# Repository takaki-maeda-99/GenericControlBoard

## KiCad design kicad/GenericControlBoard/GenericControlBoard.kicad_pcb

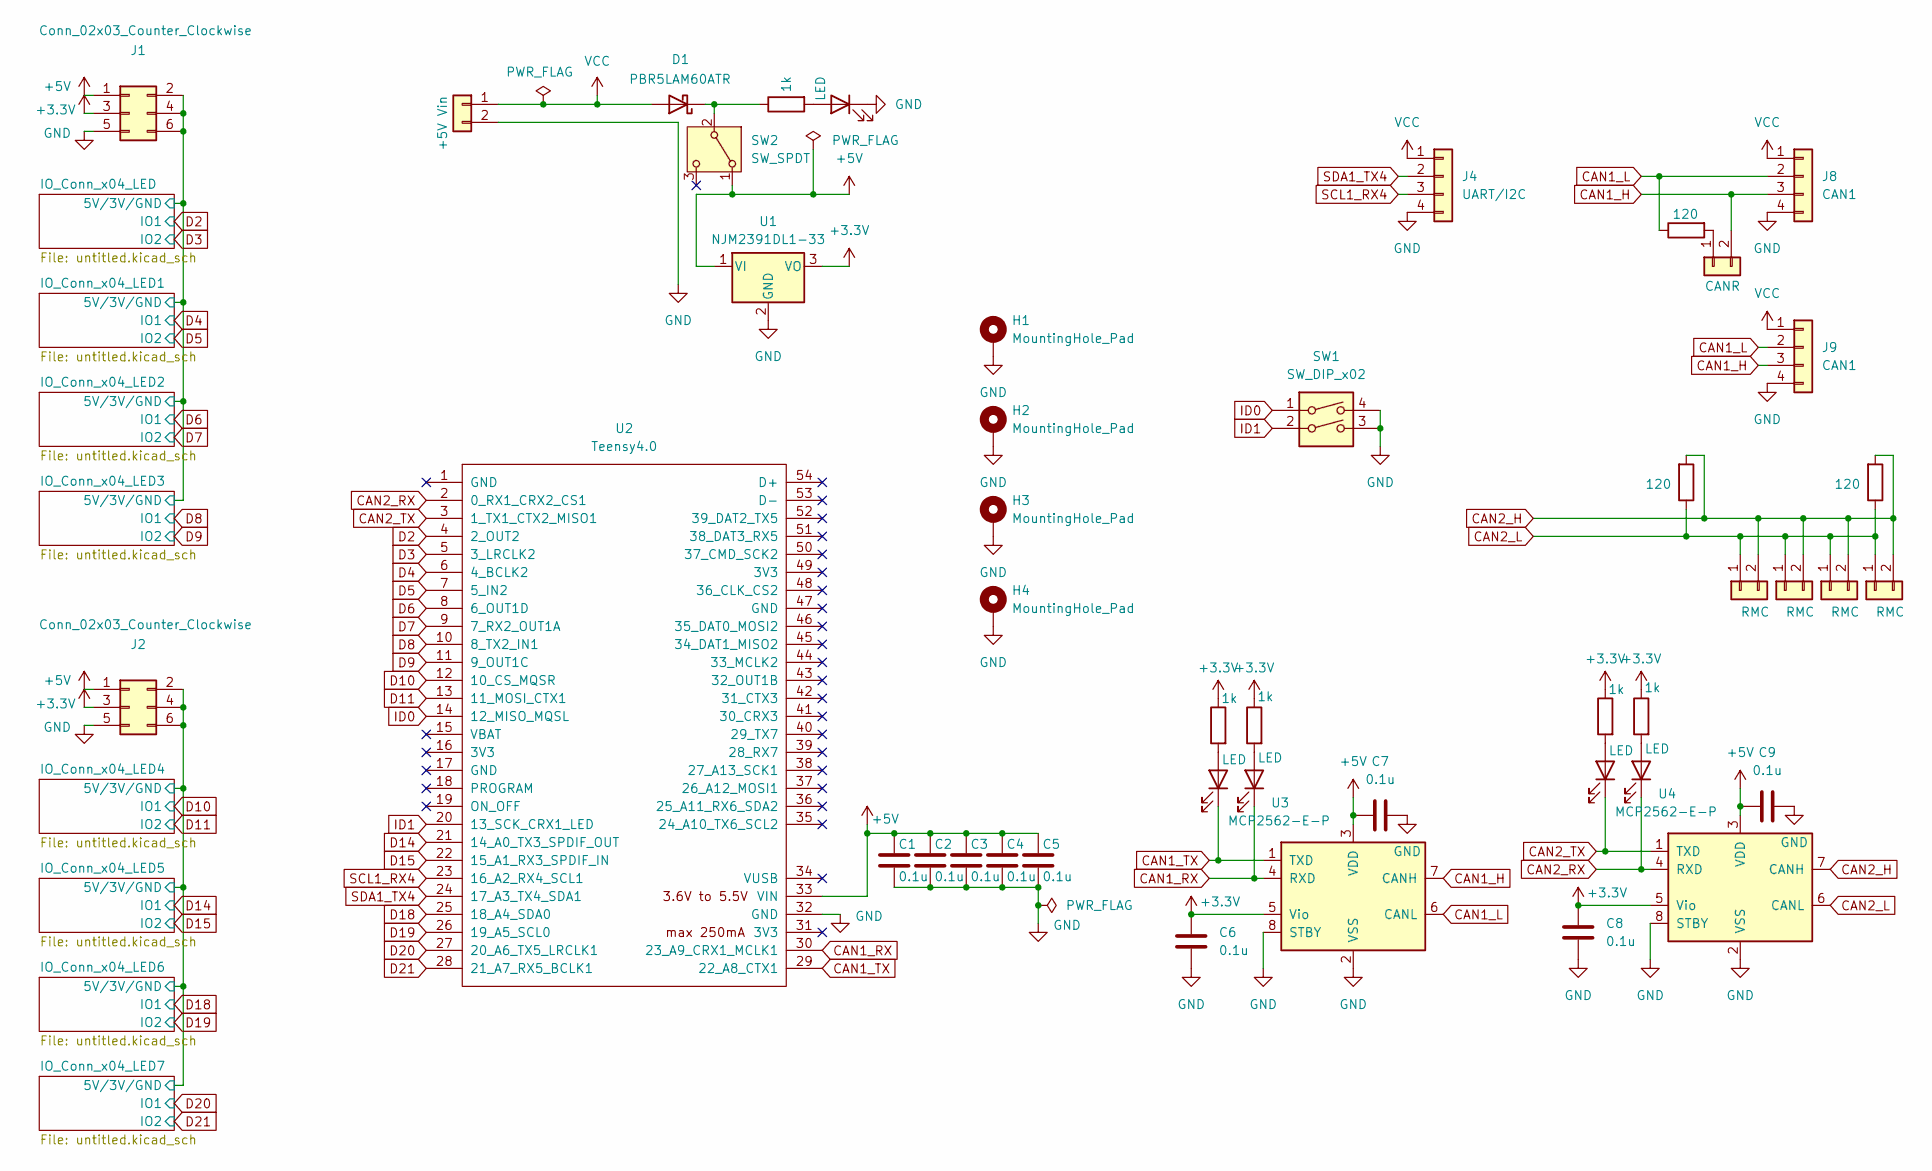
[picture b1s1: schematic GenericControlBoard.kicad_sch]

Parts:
C1, C2, C3, C4, C5, C6, C7, C8, C9: 0.1u; C_0603_1608Metric
D1: PBR5LAM60ATR; D_SOD-128
D2, D3, D22, D23, D24: LED; LED_0603_1608Metric
H1, H2, H3, H4: MountingHole_Pad; MountingHole_3.2mm_M3_DIN965_Pad
J1, J2: Conn_02x03_Counter_Clockwise; PinHeader_2x03_P2.54mm_Vertical
J3: +5V Vin; JST_XH_S2B-XH-A_1x02_P2.50mm_Horizontal
J4: UART/I2C; JST_XH_S4B-XH-A_1x04_P2.50mm_Horizontal
J5: CANR; PinSocket_1x02_P2.54mm_Vertical
J6, J7, J10, J11: RMC; JST_XH_S2B-XH-A_1x02_P2.50mm_Horizontal
J8, J9: CAN1; JST_XH_S4B-XH-A_1x04_P2.50mm_Horizontal
R1, R2, R24, R25, R26: 1k; R_0603_1608Metric
R4, R5, R7: 120; R_0603_1608Metric
SW1: SW_DIP_x02; SW_DIP_SPSTx02_Slide_9.78x7.26mm_W7.62mm_P2.54mm
SW2: SW_SPDT; FanPinHeader_1x03_P2.54mm_Vertical
U1: NJM2391DL1-33; TO-252-2
U2: Teensy4.0; Teensy40
U3, U4: MCP2562-E-P; DIP-8_W7.62mm

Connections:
+3.3V: C6.2, C8.2, J1.3, J2.3, R1.1, R2.1, R25.1, R26.1, U1.3 (VO), U3.5 (Vio), U4.5 (Vio); also elsewhere on the board
+5V: C1.1, C2.1, C3.1, C4.1, C5.1, C7.2, C9.2, J1.1, J2.1, SW2.1 (A), U1.1 (VI), U2.33 (VIN), U3.3 (VDD), U4.3 (VDD)
/IO_Conn_x04_LED4/5V/3V/GND: J2.2, J2.4, J2.6; also elsewhere on the board
/IO_Conn_x04_LED/5V/3V/GND: J1.2, J1.4, J1.6; also elsewhere on the board
CAN1_H: J5.2, J8.3, J9.3, U3.7 (CANH)
CAN1_L: J8.2, J9.2, R4.1, U3.6 (CANL)
CAN1_RX: D24.1 (K), U2.30 (23_A9_CRX1_MCLK1), U3.4 (RXD)
CAN1_TX: D23.1 (K), U2.29 (22_A8_CTX1), U3.1 (TXD)
CAN2_H: J6.2, J7.2, J10.2, J11.2, R5.2, R7.2, U4.7 (CANH)
CAN2_L: J6.1, J7.1, J10.1, J11.1, R5.1, R7.1, U4.6 (CANL)
CAN2_RX: D3.1 (K), U2.2 (0_RX1_CRX2_CS1), U4.4 (RXD)
CAN2_TX: D2.1 (K), U2.3 (1_TX1_CTX2_MISO1), U4.1 (TXD)
D2: U2.4 (2_OUT2); also elsewhere on the board
D3: U2.5 (3_LRCLK2); also elsewhere on the board
D4: U2.6 (4_BCLK2); also elsewhere on the board
D5: U2.7 (5_IN2); also elsewhere on the board
D6: U2.8 (6_OUT1D); also elsewhere on the board
D7: U2.9 (7_RX2_OUT1A); also elsewhere on the board
D8: U2.10 (8_TX2_IN1); also elsewhere on the board
D9: U2.11 (9_OUT1C); also elsewhere on the board
D10: U2.12 (10_CS_MQSR); also elsewhere on the board
D11: U2.13 (11_MOSI_CTX1); also elsewhere on the board
D14: U2.21 (14_A0_TX3_SPDIF_OUT); also elsewhere on the board
D15: U2.22 (15_A1_RX3_SPDIF_IN); also elsewhere on the board
D18: U2.25 (18_A4_SDA0); also elsewhere on the board
D19: U2.26 (19_A5_SCL0); also elsewhere on the board
D20: U2.27 (20_A6_TX5_LRCLK1); also elsewhere on the board
D21: U2.28 (21_A7_RX5_BCLK1); also elsewhere on the board
GND: C1.2, C2.2, C3.2, C4.2, C5.2, C6.1, C7.1, C8.1, C9.1, D22.1 (K), H1.1, H2.1, H3.1, H4.1, J1.5, J2.5, J3.2, J4.4, J8.4, J9.4, SW1.3, SW1.4, U1.2 (GND), U2.32 (GND), U3.2 (VSS), U3.8 (STBY), U4.2 (VSS), U4.8 (STBY); also elsewhere on the board
ID0: SW1.1, U2.14 (12_MISO_MQSL)
ID1: SW1.2, U2.20 (13_SCK_CRX1_LED)
unnamed: D1.1 (K), R24.1, SW2.2 (B)
unnamed: D2.2 (A), R1.2
unnamed: D3.2 (A), R2.2
unnamed: D22.2 (A), R24.2
unnamed: D23.2 (A), R25.2
unnamed: D24.2 (A), R26.2
unnamed: J5.1, R4.2
SCL1_RX4: J4.3, U2.23 (16_A2_RX4_SCL1)
SDA1_TX4: J4.2, U2.24 (17_A3_TX4_SDA1)
VCC: D1.2 (A), J3.1, J4.1, J8.1, J9.1

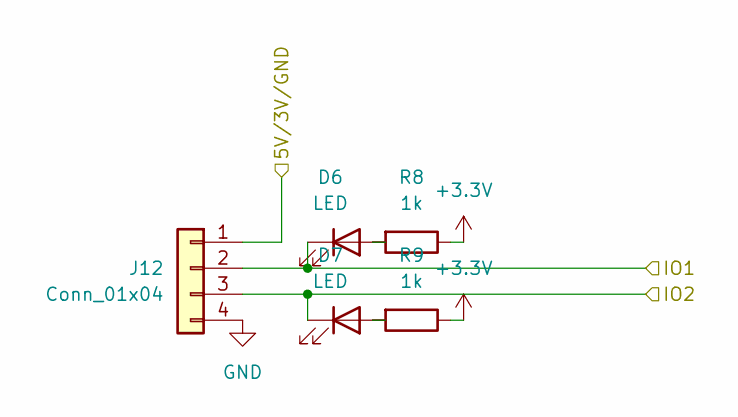
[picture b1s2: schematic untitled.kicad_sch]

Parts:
D6, D7: LED; LED_0603_1608Metric
J12: Conn_01x04; JST_XH_S4B-XH-A_1x04_P2.50mm_Horizontal
R8, R9: 1k; R_0603_1608Metric

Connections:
+3.3V: R8.1, R9.1; also elsewhere on the board
/IO_Conn_x04_LED/5V/3V/GND: J12.1; also elsewhere on the board
D2: D6.1 (K), J12.2; also elsewhere on the board
D3: D7.1 (K), J12.3; also elsewhere on the board
GND: J12.4; also elsewhere on the board
unnamed: D6.2 (A), R8.2
unnamed: D7.2 (A), R9.2

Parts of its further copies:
D8, D9, D10, D11, D12, D13, D14, D15, D16, D17, D18, D19, D20, D21: LED; LED_0603_1608Metric
J13, J14, J15, J16, J17, J18, J19: Conn_01x04; JST_XH_S4B-XH-A_1x04_P2.50mm_Horizontal
R10, R11, R12, R13, R14, R15, R16, R17, R18, R19, R20, R21, R22, R23: 1k; R_0603_1608Metric

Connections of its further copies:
+3.3V: R10.1, R11.1, R12.1, R13.1, R14.1, R15.1, R16.1, R17.1, R18.1, R19.1, R20.1, R21.1, R22.1, R23.1; also elsewhere on the board
/IO_Conn_x04_LED4/5V/3V/GND: J16.1, J17.1, J18.1, J19.1; also elsewhere on the board
/IO_Conn_x04_LED/5V/3V/GND: J13.1, J14.1, J15.1; also elsewhere on the board
D4: D8.1 (K), J13.2; also elsewhere on the board
D5: D9.1 (K), J13.3; also elsewhere on the board
D6: D10.1 (K), J14.2; also elsewhere on the board
D7: D11.1 (K), J14.3; also elsewhere on the board
D8: D12.1 (K), J15.2; also elsewhere on the board
D9: D13.1 (K), J15.3; also elsewhere on the board
D10: D14.1 (K), J16.2; also elsewhere on the board
D11: D15.1 (K), J16.3; also elsewhere on the board
D14: D16.1 (K), J17.2; also elsewhere on the board
D15: D17.1 (K), J17.3; also elsewhere on the board
D18: D18.1 (K), J18.2; also elsewhere on the board
D19: D19.1 (K), J18.3; also elsewhere on the board
D20: D20.1 (K), J19.2; also elsewhere on the board
D21: D21.1 (K), J19.3; also elsewhere on the board
GND: J13.4, J14.4, J15.4, J16.4, J17.4, J18.4, J19.4; also elsewhere on the board
unnamed: D8.2 (A), R10.2
unnamed: D9.2 (A), R11.2
unnamed: D10.2 (A), R12.2
unnamed: D11.2 (A), R13.2
unnamed: D12.2 (A), R14.2
unnamed: D13.2 (A), R15.2
unnamed: D14.2 (A), R16.2
unnamed: D15.2 (A), R17.2
unnamed: D16.2 (A), R18.2
unnamed: D17.2 (A), R19.2
unnamed: D18.2 (A), R20.2
unnamed: D19.2 (A), R21.2
unnamed: D20.2 (A), R22.2
unnamed: D21.2 (A), R23.2

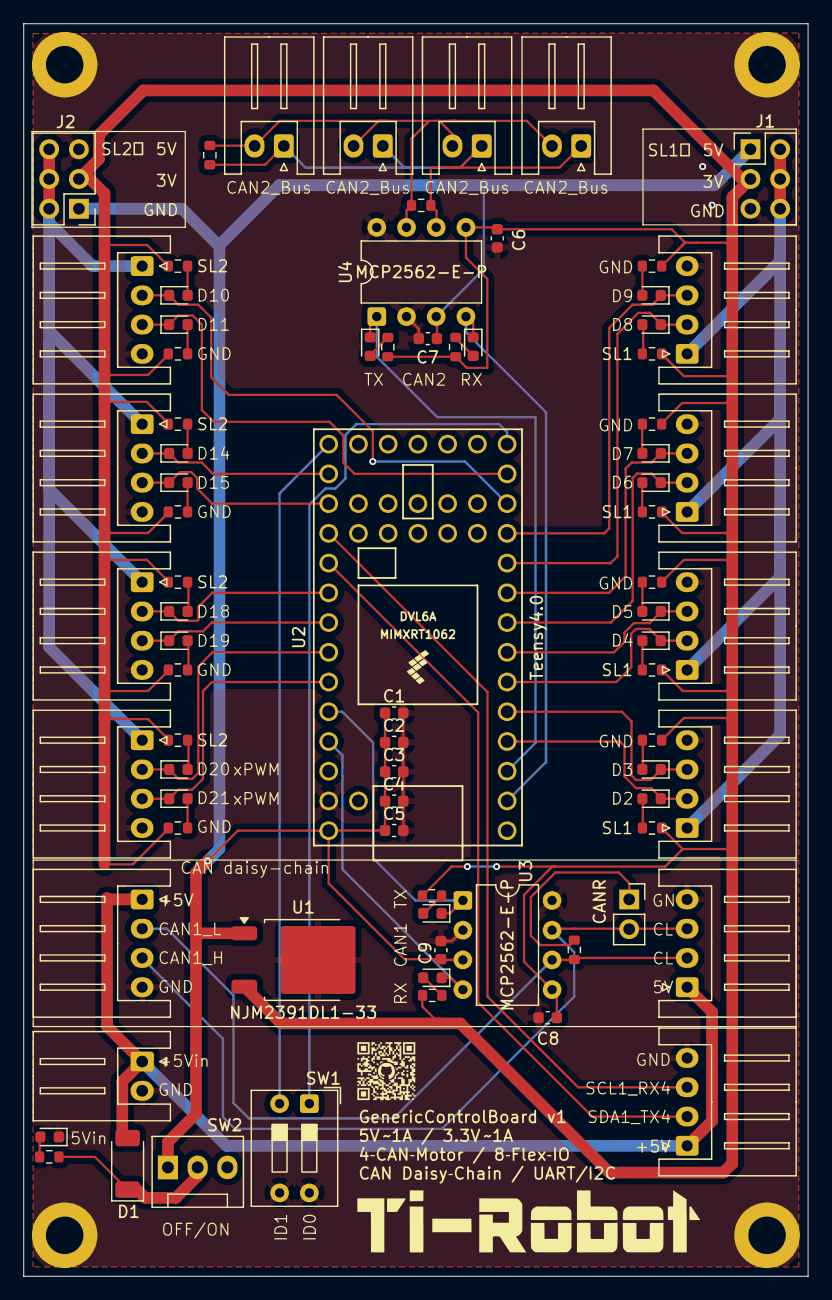
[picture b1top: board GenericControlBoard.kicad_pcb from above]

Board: 2 copper layers, 67.0 x 107.0 mm, 84 parts (0 on the bottom side), 57 nets.

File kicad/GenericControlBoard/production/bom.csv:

Designator,Footprint,Quantity,Value,LCSC Part #
"C1, C2, C3, C4, C5, C6, C7, C8, C9",0603,9,0.1u,
D1,D_SOD-128,1,PBR5LAM60ATR,
"D10, D11, D12, D13, D14, D15, D16, D17, D18, D19, D2, D20, D21, D22, D23, D24, D3, D6, D7, D8, D9",0603,21,LED,
"J1, J2",PinHeader_2x03_P2.54mm_Vertical,2,Conn_02x03_Counter_Clockwise,
"J10, J11, J6, J7",JST_XH_S2B-XH-A_1x02_P2.50mm_Horizontal,4,RMC,
"J12, J13, J14, J15, J16, J17, J18, J19",JST_XH_S4B-XH-A_1x04_P2.50mm_Horizontal,8,Conn_01x04,
J3,JST_XH_S2B-XH-A_1x02_P2.50mm_Horizontal,1,+5V Vin,
J4,JST_XH_S4B-XH-A_1x04_P2.50mm_Horizontal,1,UART/I2C,
J5,PinSocket_1x02_P2.54mm_Vertical,1,CANR,
"J8, J9",JST_XH_S4B-XH-A_1x04_P2.50mm_Horizontal,2,CAN1,
"R1, R10, R11, R12, R13, R14, R15, R16, R17, R18, R19, R2, R20, R21, R22, R23, R24, R25, R26, R8, R9",0603,21,1k,
"R4, R5, R7",0603,3,120,
SW1,SW_DIP_SPSTx02_Slide_9.78x7.26mm_W7.62mm_P2.54mm,1,SW_DIP_x02,
SW2,FanPinHeader_1x03_P2.54mm_Vertical,1,SW_SPDT,
U1,TO-252-2,1,NJM2391DL1-33,
U2,Teensy40,1,Teensy4.0,
"U3, U4",DIP-8_W7.62mm,2,MCP2561-E-P,

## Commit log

2025-08-18 fixname
2025-08-21 updateDJILib
2025-08-21 can プロトコル+モーター制御
2025-08-22 swerve check done
2025-08-22 teensy3
2025-08-23 プロトコル
2025-08-26 refactoring
